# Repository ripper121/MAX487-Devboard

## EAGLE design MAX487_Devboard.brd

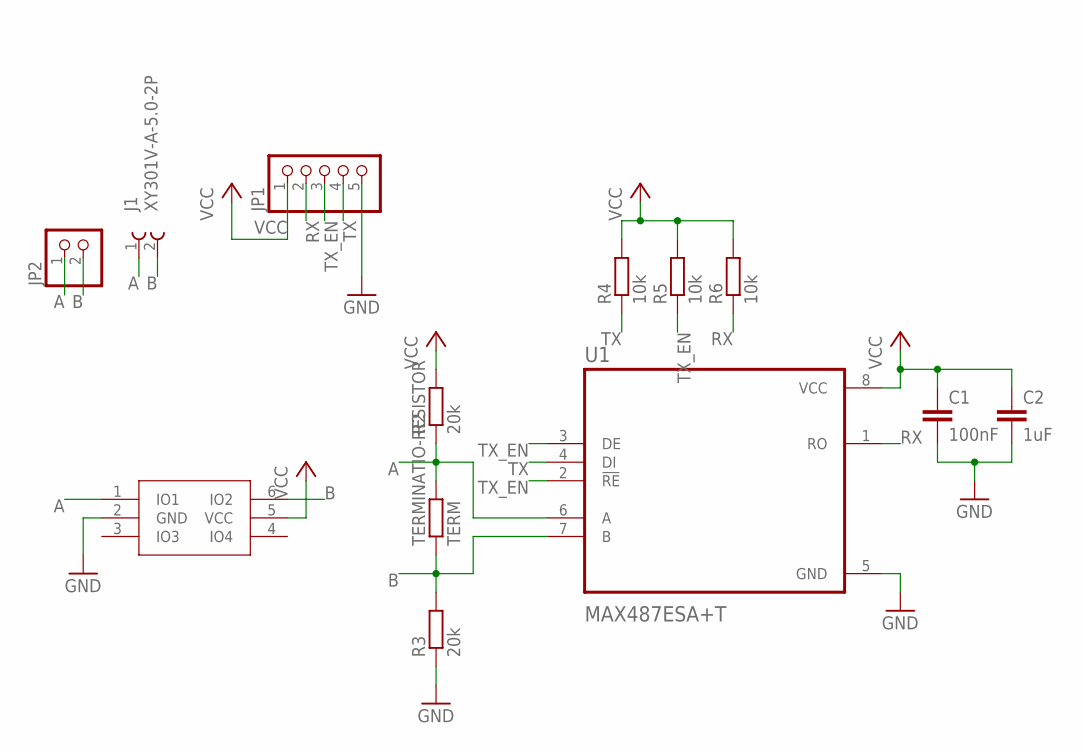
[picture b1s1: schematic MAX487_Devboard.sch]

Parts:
C1: 100nF; C0603
C2: 1uF; C0603
J1: XY301V-A-5.0-2P; 691102710002
JP1: PINHD-1X5; 1X05
JP2: PINHD-1X2; 1X02
R2, R3: 20k; R0402
R4, R5, R6: 10k; R0402
TERMINATIO-RESISTOR: TERM; R0805
U1: MAX487ESA+T; SOIC127P600X175-8N
U2: ESDU5V0H4; SOT-23-6

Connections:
A: J1.1, JP2.1, R2.1, TERMINATIO-RESISTOR.2, U1.6 (A), U2.1 (IO1)
B: J1.2, JP2.2, R3.2, TERMINATIO-RESISTOR.1, U1.7 (B), U2.6 (IO2)
GND: C1.2, C2.2, JP1.5, R3.1, U1.5 (GND), U2.2 (GND)
RX: JP1.2, R6.1, U1.1 (RO)
TX: JP1.4, R4.1, U1.4 (DI)
TX_EN: JP1.3, R5.1, U1.2 (!RE), U1.3 (DE)
VCC: C1.1, C2.1, JP1.1, R2.2, R4.2, R5.2, R6.2, U1.8 (VCC), U2.5 (VCC)

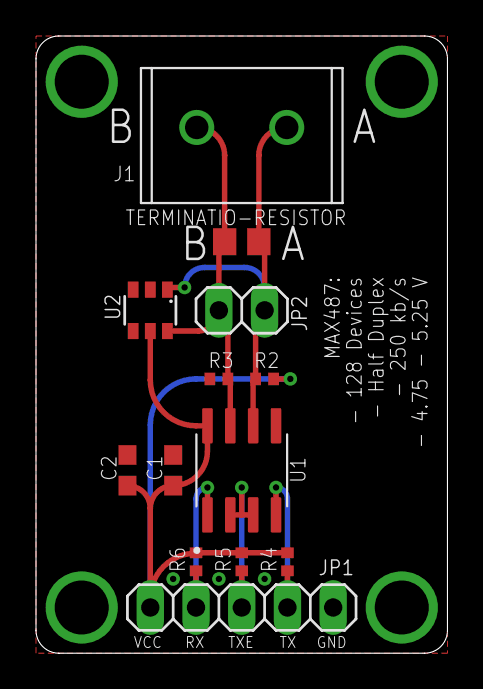
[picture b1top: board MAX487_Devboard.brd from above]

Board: 2 copper layers, 22.9 x 34.3 mm, 13 parts (0 on the bottom side), 7 nets.

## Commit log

2022-09-14 init
2022-09-14 Schematic
